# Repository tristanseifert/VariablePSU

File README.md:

VariablePSU
===========

A simple dual-channel variable power supply with lots of lovely features.

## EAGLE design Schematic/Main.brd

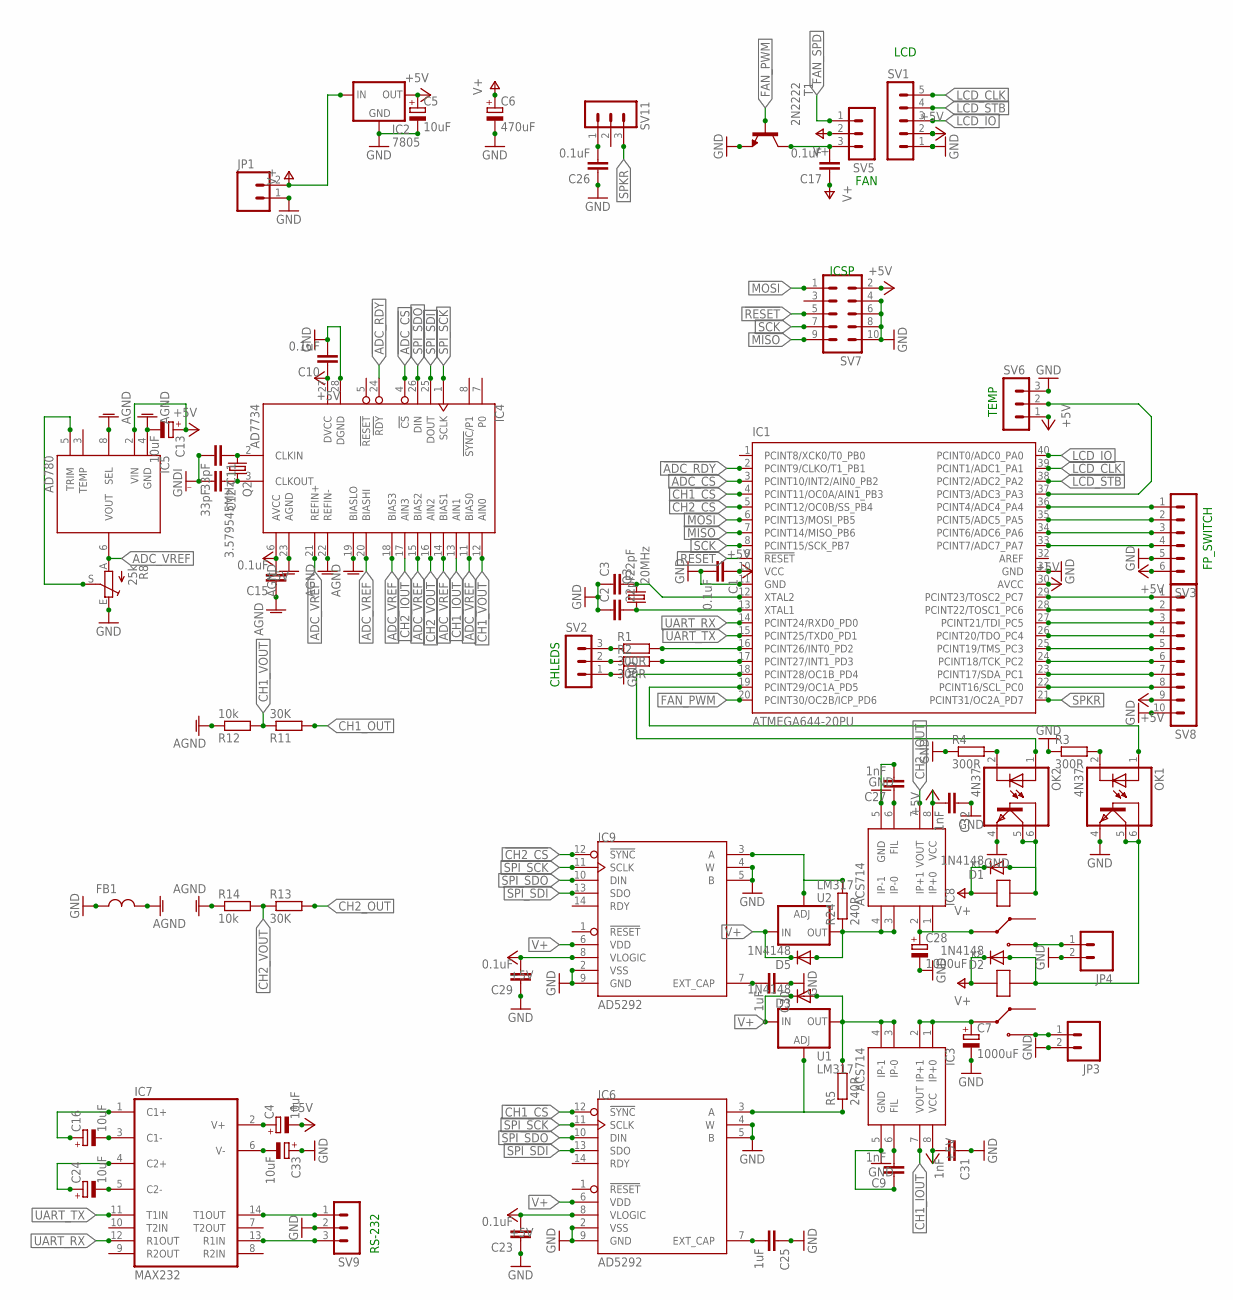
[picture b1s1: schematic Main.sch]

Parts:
C1, C10, C15, C17, C23, C26, C29: 0.1uF; C2012
C2, C3: 22pF; C025-024X044
C4, C5, C13, C16, C24, C33: 10uF; E2,5-5
C6: 470uF; E5-10,5
C7, C28: 1000uF; E5-13
C9, C27, C31, C32: 1nF; C2012
C11, C12: 33pF; C2012
C25, C30: 1uF; C2012
D1, D2, D3, D5: 1N4148; DO35-7
FB1: FERRITE2012; R2012
IC1: ATMEGA644-20PU; DIL40
IC2: 7805; 78MXXS
IC3, IC8: ACS714; SOP08
IC4: AD7734; TSSOP28
IC5: AD780; SOP08
IC6, IC9: AD5292; TSSOP14
IC7: MAX232; DIL16
JP1, JP3, JP4: M023.5MM; SCREWTERMINAL-3.5MM-2
K1, K2: SRD-24VDC-SL-C
OK1, OK2: 4N37; DIL06
Q2: 3.579545MHz; HC49/S
Q3: 20MHz; HC49/S
R1, R2, R3, R4: 300R; R2012
R5, R24: 240R; 0204/7
R8: 25k; B25P
R11, R13: 30K; R2012
R12, R14: 10k; R2012
SV1: MA05-1
SV2, SV5, SV6, SV9, SV11: MA03-1
SV3: MA06-1
SV7: MA05-2
SV8: MA10-1
T1: 2N2222; TO92
U1, U2: LM317; TO220-ADJ

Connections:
!ADC_CS!: IC1.3 (PCINT10/INT2/AIN0_PB2), IC4.4 (!CS!)
!ADC_RDY!: IC1.2 (PCINT9/CLKO/T1_PB1), IC4.24 (!RDY!)
!CH1_CS!: IC1.4 (PCINT11/OC0A/AIN1_PB3), IC6.12 (!SYNC!)
!CH2_CS!: IC1.5 (PCINT12/OC0B/SS_PB4), IC9.12 (!SYNC!)
!LCD_STB!: IC1.38 (PCINT2/ADC2_PA2), SV1.4
!RESET!: IC1.9 (!RESET), IC6.1 (!RESET!), IC9.1 (!RESET!), SV7.5
+5V: C1.1, C4.-, C5.+, C10.1, C13.+, C15.2, C23.2, C29.2, C31.2, C32.2, IC1.10 (VCC), IC1.30 (AVCC), IC2.OUT, IC3.8 (VCC), IC4.6 (AVCC), IC4.27 (DVCC), IC5.2 (VIN), IC6.8 (VLOGIC), IC8.8 (VCC), IC9.8 (VLOGIC), SV1.2, SV3.6, SV6.1, SV7.2, SV8.9
ADC_VREF: IC4.11 (BIAS0), IC4.14 (BIAS1), IC4.15 (BIAS2), IC4.18 (BIAS3), IC4.20 (BIASHI), IC4.21 (REFIN+), IC5.6 (VOUT), R8.A
AGND: C13.-, C15.1, FB1.2, IC4.19 (BIASLO), IC4.22 (REFIN-), IC4.23 (AGND), IC5.4 (GND), IC5.8 (SEL), R12.1, R14.1
CH1_IOUT: IC3.7 (VOUT), IC4.13 (AIN1)
CH1_OUT: C7.+, IC3.1 (IP+0), IC3.2 (IP+1), K2.C (IN), R11.2
CH1_VOUT: IC4.12 (AIN0), R11.1, R12.2
CH2_IOUT: IC4.17 (AIN3), IC8.7 (VOUT)
CH2_OUT: C28.+, IC8.1 (IP+0), IC8.2 (IP+1), K1.C (IN), R13.2
CH2_VOUT: IC4.16 (AIN2), R13.1, R14.2
FAN_PWM: IC1.20 (PCINT30/OC2B/ICP_PD6), T1.2 (B)
FAN_SPD: SV5.1
GND: C1.2, C2.1, C3.1, C5.-, C6.-, C26.1, C33.+, IC1.11 (GND), IC1.31 (GND), IC2.GND, IC7.15 (GND), JP1.1, JP3.2, JP4.2, OK1.4 (EMI), OK2.4 (EMI), R3.1, R4.1, R8.E, SV1.1, SV2.1, SV3.5, SV6.3, SV7.4, SV7.6, SV7.8, SV7.10, SV8.10, SV9.2, T1.1 (E)
GNDI: C7.-, C9.1, C10.2, C11.2, C12.2, C23.1, C25.1, C27.2, C28.-, C29.1, C30.1, C31.1, C32.1, FB1.1, IC3.5 (GND), IC4.28 (DGND), IC6.2 (VSS), IC6.4 (W), IC6.5 (B), IC6.9 (GND), IC8.5 (GND), IC9.2 (VSS), IC9.4 (W), IC9.5 (B), IC9.9 (GND)
LCD_CLK: IC1.39 (PCINT1/ADC1_PA1), SV1.5
LCD_IO: IC1.40 (PCINT0/ADC0_PA0), SV1.3
MISO: IC1.7 (PCINT14/MISO_PB6), SV7.9
MOSI: IC1.6 (PCINT13/MOSI_PB5), SV7.1
unnamed: C3.2, IC1.12 (XTAL2), Q3.2
unnamed: C2.2, IC1.13 (XTAL1), Q3.1
unnamed: IC1.18 (PCINT28/OC1B_PD4), OK2.1 (A)
unnamed: IC1.19 (PCINT29/OC1A_PD5), OK1.1 (A)
unnamed: IC1.37 (PCINT3/ADC3_PA3), SV6.2
unnamed: IC1.17 (PCINT27/INT1_PD3), R2.2
unnamed: R1.1, SV2.3
unnamed: R2.1, SV2.2
unnamed: C26.2, SV11.1
unnamed: IC1.33 (PCINT7/ADC7_PA7), SV3.4
unnamed: IC1.16 (PCINT26/INT0_PD2), R1.2
unnamed: IC1.29 (PCINT23/TOSC2_PC7), SV8.1
unnamed: IC1.28 (PCINT22/TOSC1_PC6), SV8.2
unnamed: IC1.27 (PCINT21/TDI_PC5), SV8.3
unnamed: OK1.2 (C), R3.2
unnamed: OK2.2 (C), R4.2
unnamed: IC1.26 (PCINT20/TDO_PC4), SV8.4
unnamed: IC1.25 (PCINT19/TMS_PC3), SV8.5
unnamed: D1.A, K1.1, OK2.5 (COL), OK2.6 (BAS)
unnamed: D2.A, K2.1, OK1.5 (COL), OK1.6 (BAS)
unnamed: D3.A, IC3.3 (IP-0), IC3.4 (IP-1), R5.2, U1.OUT
unnamed: C17.2, SV5.3, T1.3 (C)
unnamed: IC1.24 (PCINT18/TCK_PC2), SV8.6
unnamed: C9.2, IC3.6 (FIL)
unnamed: IC1.23 (PCINT17/SDA_PC1), SV8.7
unnamed: C12.1, IC4.3 (CLKOUT), Q2.2
unnamed: C11.1, IC4.2 (CLKIN), Q2.1
unnamed: IC5.5 (TRIM), R8.S
unnamed: IC1.22 (PCINT16/SCL_PC0), SV8.8
unnamed: C24.-, IC7.5 (C2-)
unnamed: C16.-, IC7.3 (C1-)
unnamed: C25.2, IC6.7 (EXT_CAP)
unnamed: IC6.3 (A), R5.1, U1.ADJ
unnamed: JP4.1, K1.NO
unnamed: JP3.1, K2.NO
unnamed: C27.1, IC8.6 (FIL)
unnamed: D5.A, IC8.3 (IP-0), IC8.4 (IP-1), R24.1, U2.OUT
unnamed: C24.+, IC7.4 (C2+)
unnamed: C30.2, IC9.7 (EXT_CAP)
unnamed: IC9.3 (A), R24.2, U2.ADJ
unnamed: C16.+, IC7.1 (C1+)
unnamed: C33.-, IC7.6 (V-)
unnamed: C4.+, IC7.2 (V+)
ROT_A: IC1.36 (PCINT4/ADC4_PA4), SV3.1
ROT_B: IC1.35 (PCINT5/ADC5_PA5), SV3.2
ROT_BTN: IC1.34 (PCINT6/ADC6_PA6), SV3.3
RS232_RX: IC7.13 (R1IN), SV9.3
RS232_TX: IC7.14 (T1OUT), SV9.1
SCK: IC1.8 (PCINT15/SCK_PB7), SV7.7
SPI_SCK: IC4.1 (SCLK), IC6.11 (SCLK), IC9.11 (SCLK)
SPI_SDI: IC4.25 (DOUT), IC6.13 (SDO), IC9.13 (SDO)
SPI_SDO: IC4.26 (DIN), IC6.10 (DIN), IC9.10 (DIN)
SPKR: IC1.21 (PCINT31/OC2A_PD7), SV11.3
UART_RX: IC1.14 (PCINT24/RXD0_PD0), IC7.12 (R1OUT)
UART_TX: IC1.15 (PCINT25/TXD0_PD1), IC7.11 (T1IN)
V+: C6.+, C17.1, D1.C, D2.C, D3.C, D5.C, IC2.IN, IC6.6 (VDD), IC9.6 (VDD), JP1.2, K1.2, K2.2, SV5.2, U1.IN, U2.IN
VCC: IC7.16 (VCC)

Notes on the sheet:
FP_SWITCH
TEMP
CHLEDS
FAN
LCD
ICSP
RS-232

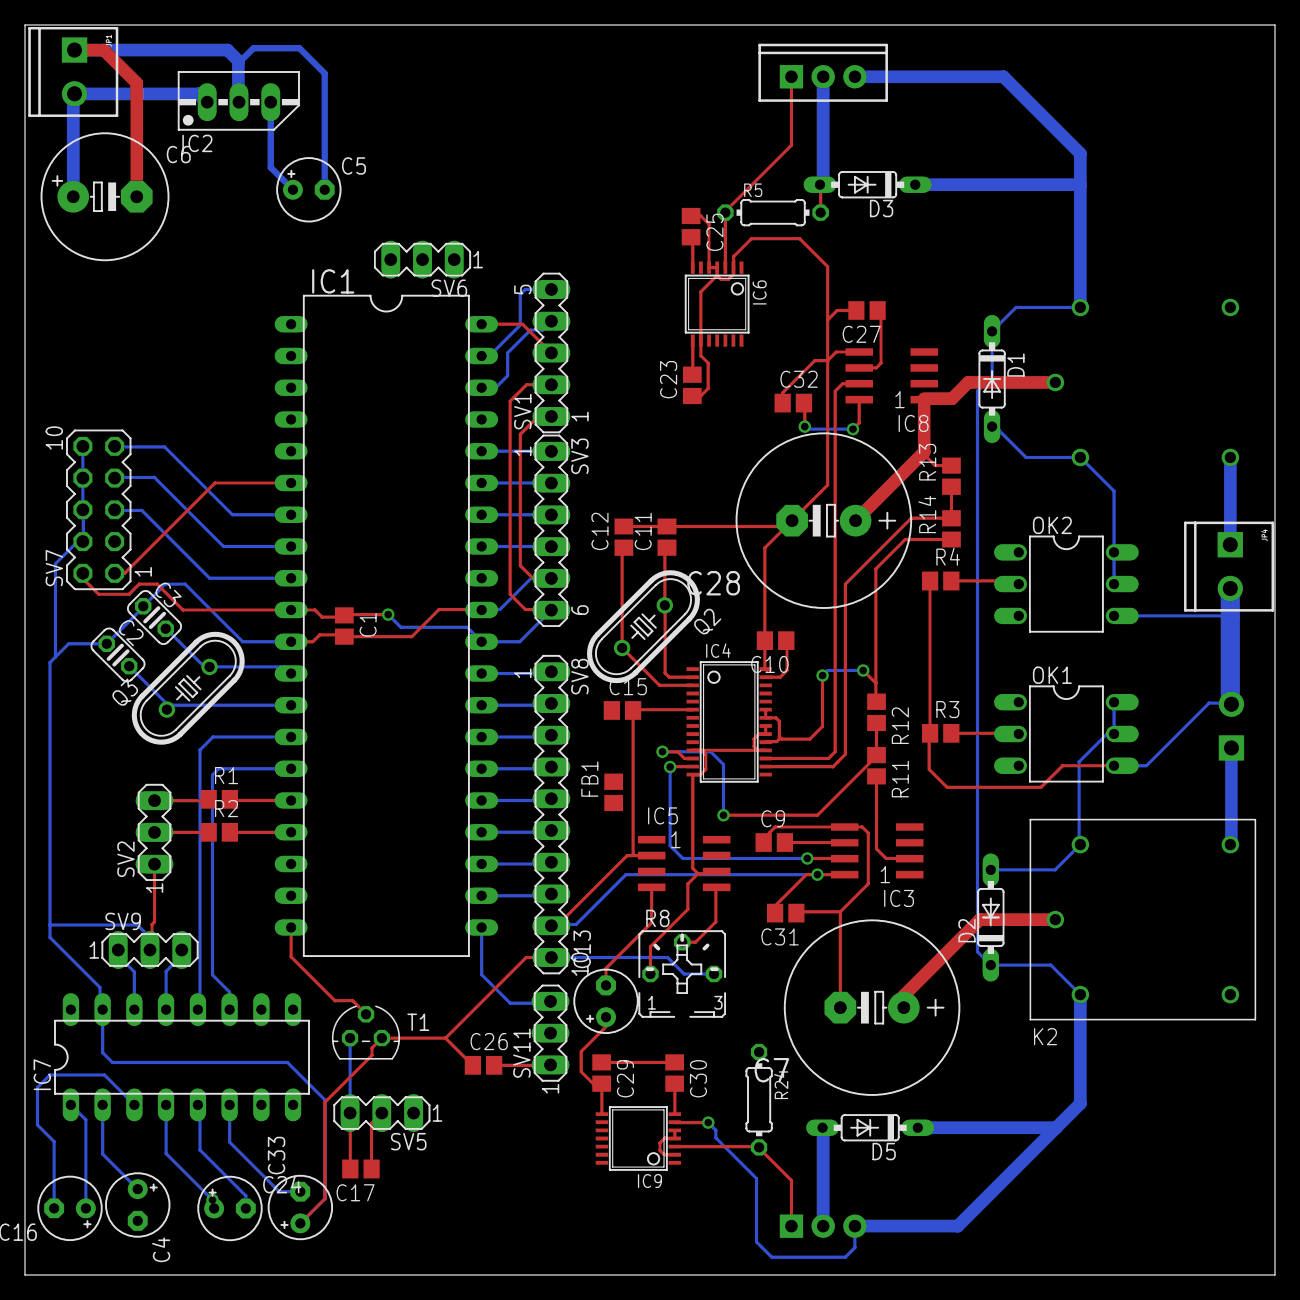
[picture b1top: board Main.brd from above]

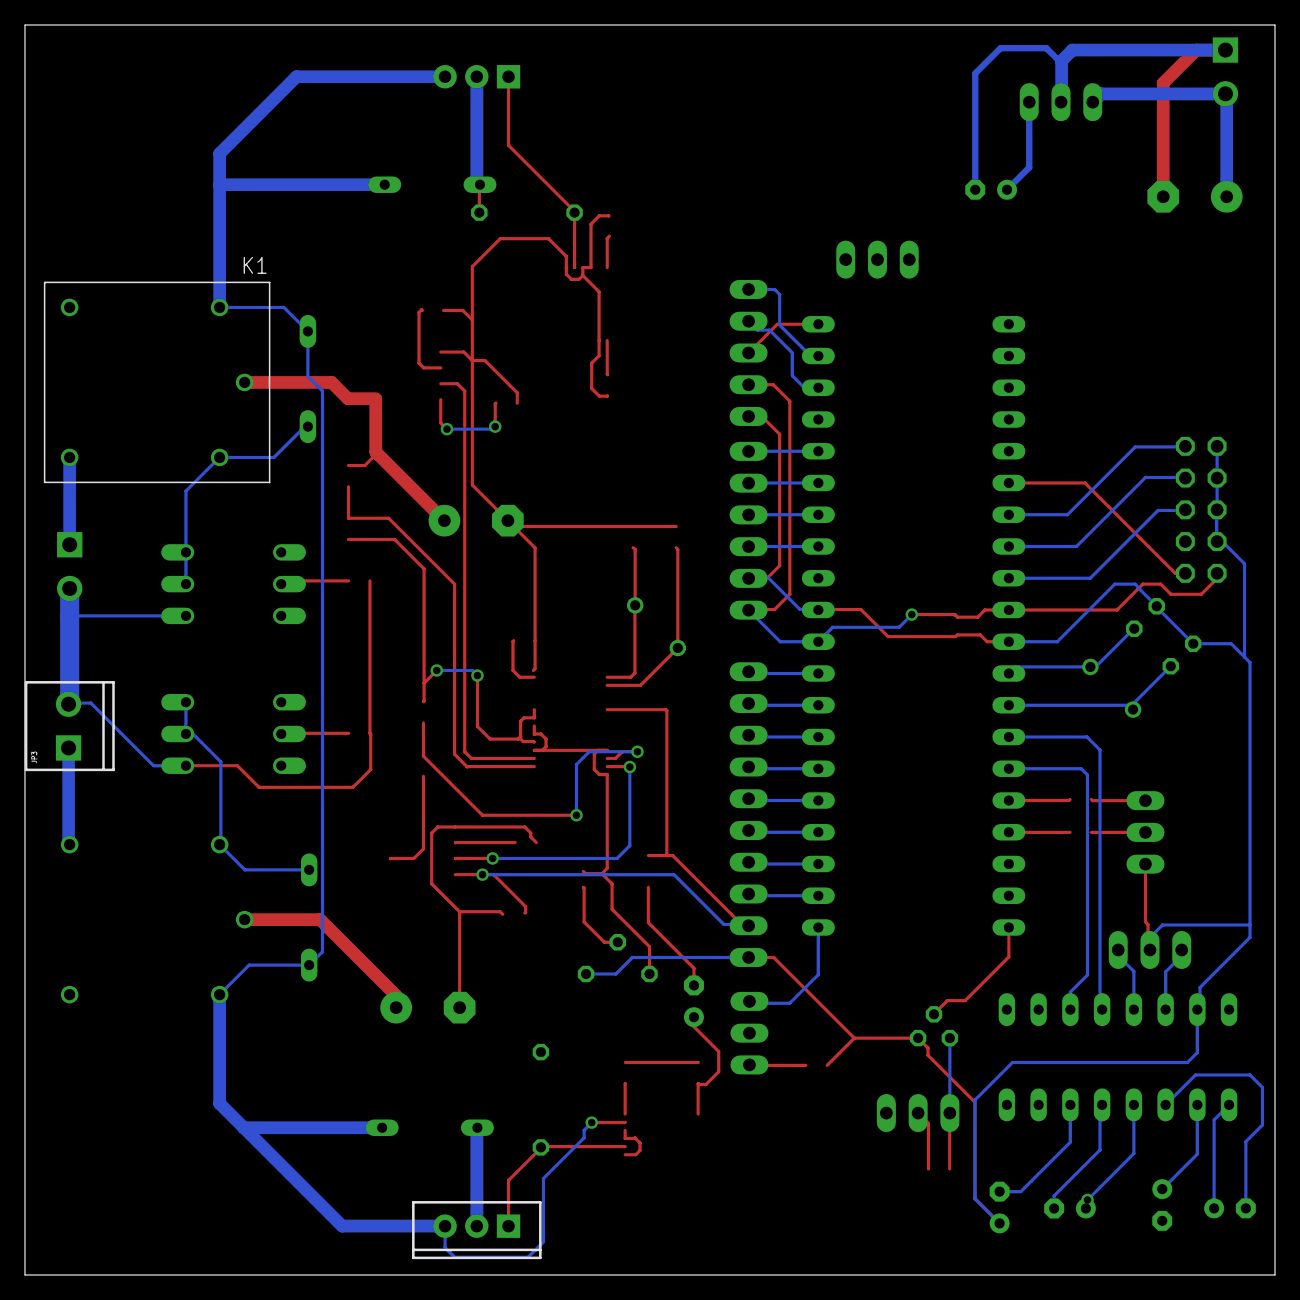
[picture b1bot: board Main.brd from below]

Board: 2 copper layers, 100.0 x 100.0 mm, 72 parts (3 on the bottom side), 78 nets.

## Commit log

2012-12-10 Initial commit of schematics 'n stuff.
2012-12-10 Blast OS X .DS_Store back to hell where they belong~
2012-12-11 Made some changes to capacitor values and such.g
2012-12-11 Added fan speed pins and temperature socket.
2012-12-12 Output components use a different gnd from input now.
2012-12-12 Moved some pins around.
2012-12-13 Added voltage out resistor dividers.
2012-12-14 Added isolation between SPI lines and ADC
2012-12-15 Added optocouplers to isolate output stuff; need separate PSU for µC stuff, second channel.
2012-12-15 Fixed LM317 bias resistor, added second 7805, etc.
2012-12-17 Got rid of the metric crapton of isolation as it wasn't really needed.
2012-12-17 Added MPLAB X project for PIC firmware.
2012-12-19 Swapped PIC for AVR.
2012-12-19 Added base firmware for AVR.
2012-12-20 Added temperature library, wrote LCD library. Main loop prints temp over serial.
2012-12-20 Added ADC_RDY interrupt handling.
2012-12-20 Connected ADC_RDY to AVR.
2012-12-21 Fixed .gitignore
2013-02-17 PCB layour and stuffs.

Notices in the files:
parts and their libraries:
SparkFun: Licensing: CC v3.0 Share-Alike You are welcome to use this library for commercial purposes.
